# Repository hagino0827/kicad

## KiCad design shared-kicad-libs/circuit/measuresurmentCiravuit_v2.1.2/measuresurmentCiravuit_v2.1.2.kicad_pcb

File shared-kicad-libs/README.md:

# shared-kicad-libs

チーム共通のKiCadライブラリを管理するリポジトリ。基板は最新バージョンのみを置き、フットプリントもまとめて登録できるようにする。

構成例:

- `footprints/` : `.pretty` フォルダや `.kicad_mod` を配置
   - 基板設計で使うフットプリントをここに集約する
- `symbols/`    : シンボルファイル（`.kicad_sym`）を配置
- `3dmodels/`   : .step 等の3Dモデルを配置
- `fp-lib-table` と `sym-lib-table` : KiCad のライブラリテーブルのサンプル
- `drc_rules.kicad_dru` : チームで共有するDRCルールの例（参考）

初回セットアップ（メンバー側）:

1. リポジトリをローカルにクローン。
2. KiCad を開き、`設定` > `パスを設定`（Preferences > Configure Paths）で変数を追加:
   - 変数名例: `TEAM_SHARED_LIBS`
   - 値例（Windows）: `C:\\Users\\you\\git\\shared-kicad-libs`
3. KiCad のライブラリ管理で `fp-lib-table` / `sym-lib-table` をグローバルまたはプロジェクトに登録する。

運用ルール（推奨）:

- `Official_Parts` と `Sandbox` を分離し、設計時は `Official_Parts` のみ使用する。
- ライブラリ変更はブランチ→PR→レビュー→マージで行う。
- PR のチェックリストに「ドリル径・ランド径・3D割当・データシート照合」を含める。

このリポジトリのファイル例をコピーして運用に合わせて編集してください。

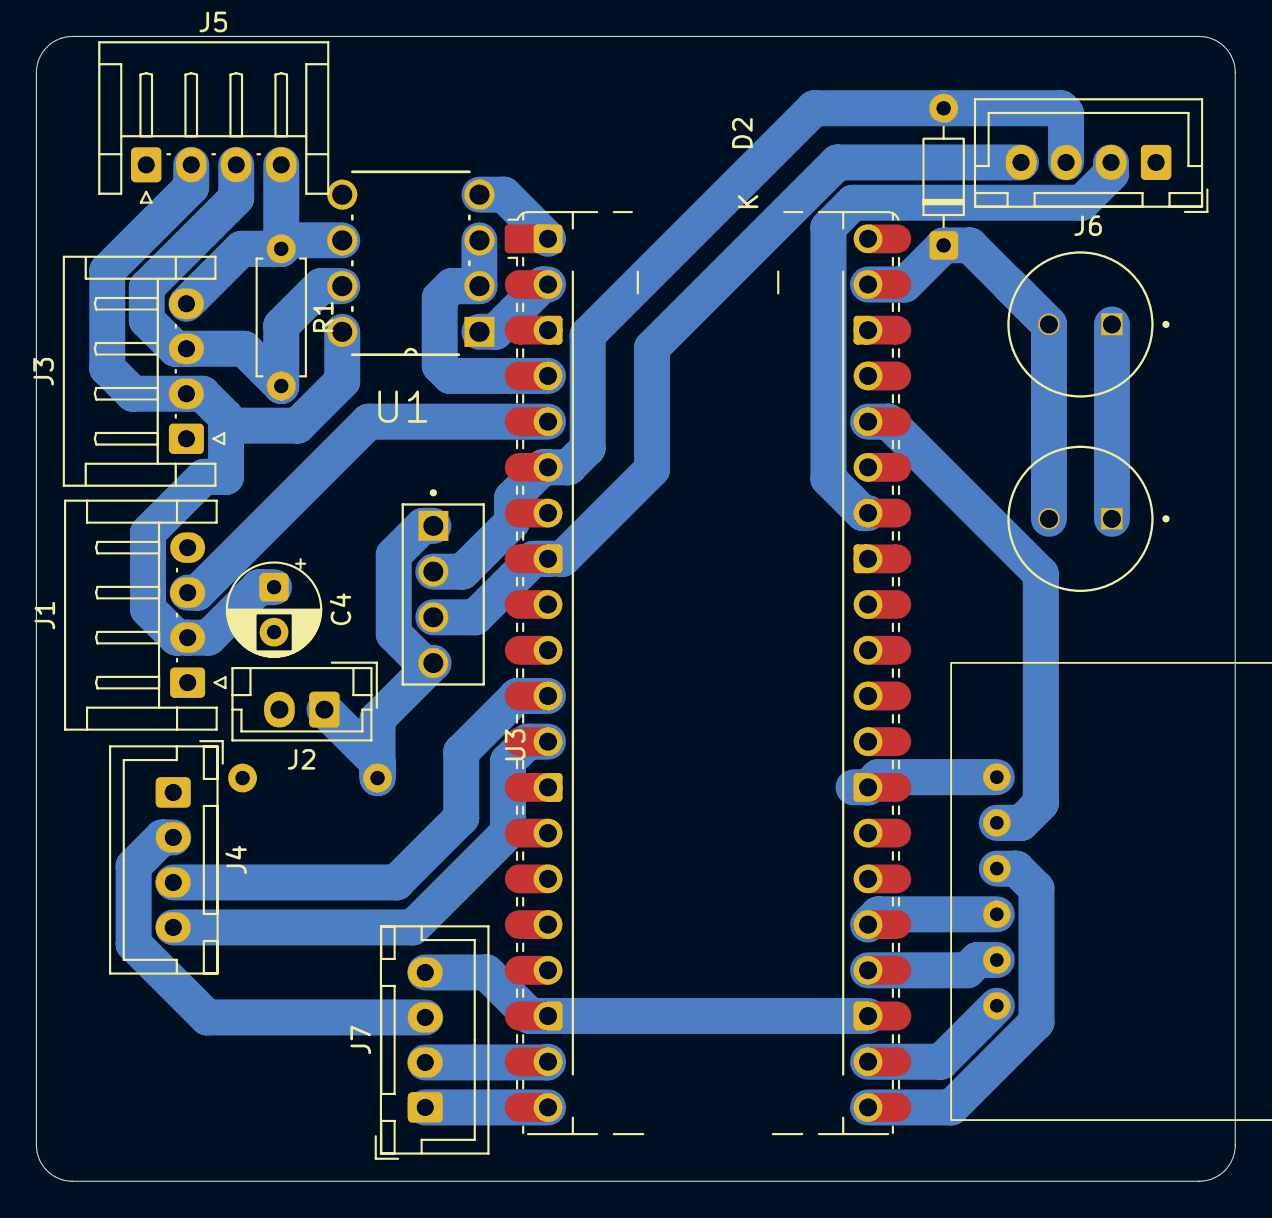
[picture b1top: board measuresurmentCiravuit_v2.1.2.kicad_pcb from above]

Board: 2 copper layers, 66.6 x 63.6 mm, 17 parts (1 on the bottom side), 20 nets.

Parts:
A1: RaspberryPi_Pico; RaspberryPi_Pico_Common_Unspecified
C1, C2: C; 1000uF C
C3: 0.33uF; C_Axial_L3.8mm_D2.6mm_P7.50mm_Horizontal
C4: 22uF; CP_Radial_D5.0mm_P2.50mm
D2: D; D_DO-35_SOD27_P7.62mm_Horizontal
J1: Airspeed; JST_EH_S4B-EH_1x04_P2.50mm_Horizontal
J2: Conn_01x02_Socket; JST_EH_B2B-EH-A_1x02_P2.50mm_Vertical
J3: RS485_BUS; JST_EH_S4B-EH_1x04_P2.50mm_Horizontal
J4: AirDataSensor; JST_XH_B4B-XH-A_1x04_P2.50mm_Vertical
J5: RS485_BUS_2; JST_EH_S4B-EH_1x04_P2.50mm_Horizontal
J6: FBW_Logger; JST_XH_B4B-XH-A_1x04_P2.50mm_Vertical
J7: GNSS_INS; JST_XH_B4B-XH-A_1x04_P2.50mm_Vertical
R1: 120; R_Axial_DIN0207_L6.3mm_D2.5mm_P7.62mm_Horizontal
U1: LTC485CN8_PBF; DIP254P762X393-8
U2: sd_card
U3: NJM2396F33

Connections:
+3.3V SD: A1.36 (3V3), U2.2 (Vcc)
FBW_RX: A1.34 (GPIO28_ADC2), J6.2
GND: A1.3 (GND), A1.8 (GND), A1.13 (GND), A1.18 (GND), A1.23 (GND), A1.28 (GND), A1.38 (GND), C1.P, C2.P, C3.2, C4.2, J1.1, J2.2, J3.1, J4.1, J5.1, J6.4, J7.4, U1.5 (GND), U2.1 (GND), U3.3 (GND)
GNSS_INS_RX: A1.20 (GPIO15), J7.1
GNSS_INS_TX: A1.19 (GPIO14), J7.2
GPIO0: A1.1 (GPIO0), U1.4 (DI)
GPIO1: A1.2 (GPIO1), U1.1 (RO)
GPIO2: A1.4 (GPIO2), U1.2 (~RE), U1.3 (DE)
GPIO3: A1.5 (GPIO3), J1.3
GPIO16: A1.21 (GPIO16), U2.3 (MISO)
GPIO17: A1.22 (GPIO17), U2.6 (CS)
GPIO18: A1.24 (GPIO18), U2.5 (SCK)
GPIO19: A1.25 (GPIO19), U2.4 (MOSI)
unnamed: A1.39 (VSYS), C1.N, C2.N, D2.1 (K)
unnamed: C3.1, J2.1, U3.1 (VIN), U3.4 (ON/OFF_CONTROL)
unnamed: J3.3, J5.3, R1.2, U1.7 (B)
unnamed: J3.4, J5.4, R1.1, U1.6 (A)
air rx: A1.11 (GPIO8), J4.3
air tx: A1.12 (GPIO9), J4.4
det: A1.6 (GPIO4), C4.1, D2.2 (A), J1.2, J3.2, J4.2, J5.2, J6.3, J7.3, U1.8 (VCC), U3.2 (VOUT)

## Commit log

2026-06-09 Create KiCad
